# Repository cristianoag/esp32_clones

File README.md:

# The Retro Hacker Clone Series

The Retro Hacker Clone Series brings together hardware designs and source-available firmware to recreate and emulate classic computers from the 1980s and 1990s using modern ESP32-S3 based hardware.

 The board is designed to feel like a small retro computer rather than a bare dev board, and the firmwares are built to be practical, tweakable, and easy to build from a standard Git checkout.

At the moment the series includes eight emulator builds on the same ESP32-S3 board:

| Firmware | Covered machines | Project |
| --- | --- | --- |
| CP400 | Prologica CP400 / CoCo 2 | [Setup guide](software/esp32_cp400_emulator/README.md) and [change log](software/esp32_cp400_emulator/docs/log.md) |
| MSX | MSX1, MSX2, and MSX2+ | [Setup guide](software/esp32_msx_emulator/README.md) and [change log](software/esp32_msx_emulator/docs/log.md) |
| MSX TurboR (experimental) | Panasonic FS-A1ST | [Setup guide](software/esp32_msxturbor_emulator/README.md), [license report](software/esp32_msxturbor_emulator/docs/licenses.md) and [change log](software/esp32_msxturbor_emulator/docs/log.md) |
| TK90X / TK95 | Microdigital TK90X (48 KiB) and TK95 | [Setup guide](software/esp32_tk95_emulator/README.md) and [change log](software/esp32_tk95_emulator/docs/log.md) |
| Apple II | Generic Apple II+ and original Apple IIe | [Setup guide](software/esp32_apple2_emulator/README.md) and [change log](software/esp32_apple2_emulator/docs/log.md) |
| Macintosh Plus | Apple Macintosh Plus | [Setup guide](software/esp32_macplus_emulator/README.md) and [change log](software/esp32_macplus_emulator/docs/log.md) |
| Sega Master System | Sega Master System (NTSC / PAL) | [Setup guide](software/esp32_sms_emulator/README.md) and [change log](software/esp32_sms_emulator/docs/log.md) |
| Commodore 64 | Commodore 64 (PAL) | [Setup guide](software/esp32_c64_emulator/README.md), [licenses](software/esp32_c64_emulator/docs/licenses.md) and [change log](software/esp32_c64_emulator/docs/log.md) |

> **Development status:** all firmwares are under active development and at different maturity stages. The CP400 and MSX firmwares are the most mature; the others (including the experimental MSX TurboR) are earlier-stage and may be incomplete or change significantly.

All eight builds share the same board, VGA output, USB keyboard input, SD-card storage, and a simple F12 menu for setup and firmware updates.

## User guides

- [Quick Start](docs/quick-start.md): connect the monitor, keyboard and
  joysticks, turn on/reset the computer, and switch firmware through F12.
- [User Manual](docs/user-manual.md): SD-card preparation, controller
  compatibility, game-loading steps for all eight firmwares, and troubleshooting.

### Switching emulators

With the current updater and shared dual 4 MiB OTA layout installed, open
**F12 > Firmware update** in any emulator and select another emulator's
`.FLH` package. For example, MSX can install CP400, and CP400 can then
install Apple II. No renaming is needed. Copy the packages to the FAT32
card root (required by CP400's file picker), prepare the destination
emulator's ROMs using its setup guide, confirm the update and keep power
connected until the board restarts. The original FLH stays on the card.

Build packages with `make firmware` in each firmware folder. Older MSX,
TK and Apple updaters reject other emulator filenames: first update to
the current build of the **same** emulator. Older CP400 installations use
a smaller partition layout and require a **one-time UART upload** of a
current build before switching via SD. FLH updates replace only the
application, not the bootloader or partition table. Use current builds
for every destination so switching remains available after reboot.
Checksums detect corruption, not authenticity; install only trusted
firmware built for this board.

After building all eight packages, run
`powershell -ExecutionPolicy Bypass -File .\software\Test-FirmwareCompatibility.ps1`
to check the shared layout and all 64 source/destination combinations
against mock OTA storage. Physical-board switching still needs validation.

## Commodore 64

The [C64 firmware](software/esp32_c64_emulator/README.md) adapts the
CPU, CIA, VIC-II and SID from
[retroelec/T-HMI-C64](https://github.com/retroelec/T-HMI-C64) to the shared
VGA board. It includes a USB C64 keyboard matrix, two calibrated USB
joysticks with port swapping, PWM sound, PRG loading, read-only D64 program
extraction, the F12 configuration menu and interchangeable FLH firmware.
Supply your own BASIC, KERNAL and character ROMs. The initial version
does not emulate a 1541 drive, cartridges or tapes, and does not claim
cycle accuracy or verified physical-board performance.

## Why this exists

The goal is not to produce a display piece. This is meant to be a useful, buildable retro-computing emulation based platform: something that captures the character of a classic computer without needing a pile of original hardware on the bench.

The project sits between hardware design, emulator work, and preservation. It keeps the board layout, software, and documentation together in one place so someone can build, test, and modify it without digging through a dozen disconnected repos.

## CP400

The Prologica CP400 was one of the more recognizable Brazilian home computers of the 1980s. It was compatible with the Tandy/Radio Shack TRS-80 Color Computer 2, but it had its own industrial design, Brazilian-language software ecosystem, and local hardware expectations.

The [CP400 firmware](software/esp32_cp400_emulator/README.md) recreates that environment on ESP32-S3 hardware, including MC6809 emulation, VGA output, native USB keyboard support, joystick inputs, SD storage, virtual floppy handling, and the F12 configuration/update menu.

## MSX

The MSX has a very special place in Brazilian computing history. It officially arrived in Brazil in 1985 through two locally produced machines: the HotBit, from Sharp/Epcom, and the Expert, from Gradiente. At a time when Brazil’s computer market was heavily restricted and imported machines were difficult and expensive to obtain, the MSX became one of the country’s most important home-computing platforms. Its standardized architecture, large software library, expandability, and built-in BASIC introduced an entire generation not only to games, but also to programming, electronics, and computer technology. 

The [MSX firmware](software/esp32_msx_emulator/README.md) runs the original fMSX core on the same shared board. It includes multiple BIOS profiles for Omega MSX2+, Gradiente Expert 1.1, Sharp Hotbit 1.2, and Panasonic FS-A1WSX / FS-A1F / FS-A1FX.

The software supports the core MSX experience with USB keyboard input, graphics, sound, cartridge booting, and firmware updates through the on-screen menu. and... USB joystick support, of course.

The F12 Media menu attaches writable `.dsk` images to drives A/B and read-only `.cas` tapes, with ejection, tape rewind and optional saved boot defaults. Disk access requires a compatible user-supplied disk BIOS; see the [disk and tape setup guide](software/esp32_msx_emulator/README.md#disk-and-tape-images).

## MSX TurboR / Panasonic FS-A1ST

The experimental [MSX TurboR firmware](software/esp32_msxturbor_emulator/README.md)
recreates the Panasonic FS-A1ST using a source subset of blueMSX, separate
from the ordinary fMSX-based MSX build. It includes Z80/R800 switching,
DRAM mode, V9958 graphics, PSG, MSX-MUSIC, PCM output and writable
360/720 KiB `.dsk` images through the original disk interface.

Supply your own FS-A1ST firmware and Kanji ROMs under
`msxturbor/bios/fs-a1st` on the FAT32 card. See the
[SD card and ROM setup](software/esp32_msxturbor_emulator/README.md#prepare-the-sd-card),
[scope and limitations](software/esp32_msxturbor_emulator/README.md#implementation-scope-and-limitations)
and [licenses and provenance](software/esp32_msxturbor_emulator/docs/licenses.md).
The original BIOS boots into MSX BASIC in host tests; physical-board
performance, VGA/audio quality and firmware switching still require
validation. A1GT/MIDI and full-speed emulation are not claimed.

## TK90X / TK95

The Microdigital TK90X and TK95 brought the ZX Spectrum family of computers to Brazilian homes. The [TK firmware](software/esp32_tk95_emulator/README.md) emulates the TK95 and 48 KiB TK90X on the same shared ESP32-S3 board, using
the cycle-stepped chips Z80 core.

The firmware includes VGA output, USB keyboard input, beeper audio and two USB joystick ports with calibration and selectable Kempston, Sinclair 1/2 or Cursor interfaces. The F12 menu brings together machine and ROM selection, 50/60 Hz Microdigital ULA timing, Portuguese/Spanish ROM language selection, sound and volume, saved boot defaults, reset options and firmware updates.

Media support includes read-only standard `.tap` playback and loading 48K `.sna` and `.z80` snapshots. Supply legally obtained, raw 16 KiB ROMs at `tk\bios\tk95.rom` and `tk\bios\tk90.rom` on the FAT32 card; the `tk` folder can sit alongside `msx` and `cp400`. No ROM bytes are embedded in the firmware.

See the [SD card and ROM setup](software/esp32_tk95_emulator/README.md#sd-card-and-roms) and [keyboard guide](software/esp32_tk95_emulator/README.md#keyboard-and-joysticks) for the original TK keyword-entry conventions.

The initial release does not include AY audio, Betadisk, TZX, tape recording or snapshot saving, and does not claim full cycle accuracy. 

## Apple II

The [Apple II firmware](software/esp32_apple2_emulator/README.md) adds generic
Apple II+ (64 KiB with language card) and original Apple IIe (128 KiB)
profiles. It follows the shared standalone PlatformIO, board-driver, F12
configuration and FLH firmware-update conventions.

The initial integration uses
[codesafe/ESP32-VGA_AppleII_Emulator](https://github.com/codesafe/ESP32-VGA_AppleII_Emulator)
as its starting reference, with a cycle-stepped NMOS 6502 and additional
IIe banking and display support. VGA preserves the full width of
80-column text; USB keyboard, calibrated joystick/paddle input, speaker
audio and two read-only NIB Disk II drives are included.

Supply machine and Disk II ROMs under `apple2/bios` on SD. No ROMs or games
are distributed. Enhanced IIe/65C02 and Brazilian TK2000, TK3000/Compact,
MC-4000/Exato and Exato IIe profiles are not claimed as supported without
their required hardware and verified ROMs. See the
[scope and limitations](software/esp32_apple2_emulator/README.md#supported-media-and-limitations).
Physical-board validation is still pending.

## Macintosh Plus

The [Macintosh Plus firmware](software/esp32_macplus_emulator/README.md)
integrates a Musashi 68000 and Macintosh peripheral core with 4 MiB of
emulated RAM, a native 512x342 monochrome image centered on 640x480 VGA,
USB keyboard input, mono audio and the shared F12 menu and FLH updater.
A direct low-speed HID boot mouse connects to **joystick port 2**;
full-speed-only mice and USB hubs are unsupported.

Supply an unmodified 128 KiB Macintosh Plus ROM and a bootable whole
SCSI disk image under `macplus/bios` and `macplus/disks` on the FAT32 card.
No Apple ROM, operating system or disk image is bundled. See the
[SD card, ROM and disk setup](software/esp32_macplus_emulator/README.md#sd-card-and-rom),
[mouse compatibility](software/esp32_macplus_emulator/README.md#mouse-compatibility)
and [scope and validation](software/esp32_macplus_emulator/README.md#scope-and-validation).
This is an initial integration, not a claim of full-speed or cycle-accurate
emulation; floppy-media support is not implemented.

## Repository layout

```text
hardware/esp32_clones/          KiCad PCB and shared board files
hardware/esp32_clones/libraries Local KiCad symbols and footprints
hardware/esp32_clones/bom       Interactive BOM and BOM assets
hardware/cases/standard/       Parametric printed base, acrylic lid and manufacturing exports
software/esp32_cp400_emulator/  PlatformIO firmware for the CP400 build
software/esp32_msx_emulator/    MSX firmware and setup files
software/esp32_msxturbor_emulator/ MSX TurboR / Panasonic FS-A1ST firmware and setup files
software/esp32_tk95_emulator/   TK90X/TK95 firmware and setup files
software/esp32_apple2_emulator/ Apple II+/original IIe firmware and setup files
software/esp32_macplus_emulator/ Macintosh Plus firmware and setup files
images/                         Generated images and project documentation assets
```

## Board renderings

For the first enclosure prototype, see the
[standard case manufacturing files and engineering report](hardware/cases/standard/README.md).
P4 combines a printed base with easy-loading PCB nut traps, a screw-fastened
upper and a drilled 3 mm acrylic lid. Four M3 x 25 nylon screws pass down through
the acrylic into base nuts. Its vented alternative uses a separate matching
base with recessed bottom-entry screws and upper nuts. The acrylic cutting
pattern is [lid.dxf](hardware/cases/standard/lid.dxf); do not reuse the old
plain panel. See the report for dimensions and remaining physical-fit checks.

The Hotbit-inspired **Compact Classic C6** fits the same PCB in a
**124 x 74 x 39.1 mm** case, reducing the earlier Classic footprint by 26.9%.
It retains the miniature keyboard, photo-inspired colours and closed decorative
grille, with underside M3 cover screws. Use the matching
[base STL](hardware/cases/hb-8000/classic_base.stl) and
[upper STL](hardware/cases/hb-8000/classic_upper.stl); do not mix these with older
Classic or Wasteland halves. See the
[assembled/exploded preview](hardware/cases/hb-8000/classic_preview.png).
Print both STLs at 100%; the upper needs removable interior supports.
PCB screws remain M3 x 8 with 1 mm nylon washers; cover screws are M3 x 25 nylon,
with four M3 hex nuts for each set. Physical plug-fit and thermal tests are
still required; the decorative grille is not a ventilation opening.

The [Sony S2](hardware/cases/sony/README.md),
[Panasonic P2](hardware/cases/panasonic/README.md) and
[Apple II A3](hardware/cases/apple2/README.md) now share the C6 base and its
bottom-entry shell fastening. Their matching uppers replace the old clip joints.

The [Mac Plus-inspired M1](hardware/cases/mac/README.md) uses the same C6 base
under a **124 x 74 x 146.1 mm upright tower**, with a separate dark decorative
screen and miniature keyboard. Its blind floppy-slot detail, top grilles and
handle-shaped recess follow the supplied visual reference; no working display,
keyboard electronics or load-bearing handle is included. See the
[assembly and print-layout preview](hardware/cases/mac/mac_preview.png).

The [CP400-inspired CP1](hardware/cases/cp400/README.md) also reuses the C6
base in the compact **124 x 74 x 39.1 mm** envelope. Its left keyboard, raised
right panel and horizontal rear grilles follow the supplied photograph.
Integral and separate-keyboard upper options are available; red/green/cyan
accents in the [preview](hardware/cases/cp400/cp400_preview.png) are a painting
guide, not separate key pieces.

The [Master System-inspired SMS1](hardware/cases/sms/README.md) uses the same
C6 base and **124 x 74 x 39.1 mm** envelope, with an angular black console
shell and one separately printed red top-panel/front-stripe insert.
Cartridge/card slots and control shapes are decorative; no joystick or
controller is modelled. See the
[assembly and print-layout preview](hardware/cases/sms/sms_preview.png).

The PCB below is the current KiCad board layout for the shared ESP32 clone board. The front and back views are generated directly from the project PCB.

<div align="center">

</div>

For the full component-by-component assembly view, open the [interactive BOM](https://htmlpreview.github.io/?https://raw.githubusercontent.com/cristianoag/esp32_clones/blob/main/hardware/esp32_clones/bom/ibom.html).

## Hardware summary

The board is built around an ESP32-S3 DevKitC-style N16R8 module with 16 MB flash and 8 MB OPI PSRAM. It includes VGA output, a USB keyboard port, SD/MMC storage, a mono audio output, and a compact layout intended to behave more like a small computer than a bare dev board.

The shared board is used by all six firmware projects, and the pin mapping is documented in the [MSX hardware section](software/esp32_msx_emulator/README.md#hardware), the [MSX TurboR hardware section](software/esp32_msxturbor_emulator/README.md#hardware-and-dependencies), the [TK hardware section](software/esp32_tk95_emulator/README.md#hardware), the [Apple II hardware section](software/esp32_apple2_emulator/README.md#hardware) and the [Macintosh Plus hardware section](software/esp32_macplus_emulator/README.md#hardware).

## BOM and purchasing

This is the current BOM for the board as defined in the KiCad project. The table is meant to be a quick parts reference for ordering and build prep.

| Component | Description | Qty | Package | AliExpress |
| --- | --- | ---: | --- | --- |
| C1 | 220 µF electrolytic capacitor | 1 | 6.3x3 mm | [AliExpress](https://s.click.aliexpress.com/e/_c3vZZzuN) |
| C2 | 10 µF electrolytic capacitor | 1 | 5x4.5 mm | [AliExpress](https://s.click.aliexpress.com/e/_c3vZZzuN) |
| C4 | 100 nF ceramic capacitor | 1 | 0805 | [AliExpress](https://s.click.aliexpress.com/e/_c31gzw17) |
| C6 | 47 nF ceramic capacitor | 1 | 0805 | [AliExpress](https://s.click.aliexpress.com/e/_c31gzw17) |
| F1 | Resettable fuse / polyfuse | 1 | 1210 | [AliExpress](https://s.click.aliexpress.com/e/_c36cHi81) |
| J1 | DC barrel jack | 1 | Horizontal | [AliExpress](https://s.click.aliexpress.com/e/_c3D102dx) |
| J2 | Micro SD card socket | 1 | uSD | [AliExpress](https://s.click.aliexpress.com/e/_c3odXI41) |
| J3 | 3.5 mm audio jack | 1 | PJ-307 | [AliExpress](https://s.click.aliexpress.com/e/_c4DX94lF) |
| J4 | 12V power header / connector | 1 | PS-12E05 | [AliExpress](https://s.click.aliexpress.com/e/_c42cnGRn) |
| J5 | 5V power header / connector | 1 | PS-22F05 | [AliExpress](https://s.click.aliexpress.com/e/_c35YnsCh) |
| J6–J8 | USB-A connector | 3 | TE 6364372-2 | [AliExpress](https://s.click.aliexpress.com/e/_c4afTAHb) |
| J9 | DB15 video connector | 1 | D-sub 15-pin | [AliExpress](https://s.click.aliexpress.com/e/_c3K7eRWv) |
| R1, R4, R7 | 10 kΩ resistor | 3 | 0805 | [AliExpress](https://s.click.aliexpress.com/e/_c2zrvGiH) |
| R8, R10, R12 | 1.2 kΩ resistor | 3 | 0805 | [AliExpress](https://s.click.aliexpress.com/e/_c2zrvGiH) |
| R9, R11, R13 | 560 Ω resistor | 3 | 0805 | [AliExpress](https://s.click.aliexpress.com/e/_c2zrvGiH) |
| R2, R5 | 330 Ω resistor | 2 | 0805 | [AliExpress](https://s.click.aliexpress.com/e/_c2zrvGiH) |
| U1 | ESP32-S3-WROOM-1 module | 1 | ESP32-S3-WROOM-1 | [AliExpress](https://s.click.aliexpress.com/e/_c2uppnEv) |

## Firmware build notes

All six firmware projects use PlatformIO with the Arduino framework and a pinned `espressif32@6.11.0` platform. From the project directory you want to use, run:

```powershell
Set-Location .\software\esp32_cp400_emulator
# or:
# Set-Location .\software\esp32_msx_emulator
# or:
# Set-Location .\software\esp32_msxturbor_emulator
# or:
# Set-Location .\software\esp32_tk95_emulator
# or:
# Set-Location .\software\esp32_apple2_emulator
# or:
# Set-Location .\software\esp32_macplus_emulator

make firmware
```

The build produces FLH packages for each target; the project directories keep their own firmware images and configuration.
From `software`, run `make` to prepare the shared SD-card tree and copy each
emulator's highest-versioned `dist\ESP32_*-X.YY.FLH` package only to the root of
`software\sdcard`. Firmware packages are copied
after merging the SD-card trees, including with parallel `make`.
Run `make firmware` there to copy packages only, or `make sdcard`
to prepare the SD-card tree only. Packages are not rebuilt; if any emulator is
missing a package, copying fails before any firmware files are deleted or copied.
Before copying, all FLH files directly in the shared SD-card root are deleted,
leaving only the latest package for each emulator. Emulator project roots and
`dist` archives are left unchanged, as are non-FLH files and nested folders
during firmware copying.
Each firmware directory includes its own board definitions and required
library sources and can be copied and compiled independently of the others.
All six still require PlatformIO and the configured ESP32 toolchain.

## ROMs and original software

Original CP400, CoCo, MSX, MSX TurboR, TK90X/TK95, ZX Spectrum, Apple II, Macintosh Plus, BASIC, cartridge, cassette, floppy and hard-disk software may still be copyrighted. This repository is for original hardware, firmware, and project files. Use legally obtained ROMs and software images when needed.

The CP400 firmware loads its BIOS files from `software/esp32_cp400_emulator/sdcard/cp400/bios`. Copy the `cp400` folder to the root of the microSD card so the firmware can read the BASIC, Extended BASIC, and CP400 or CoCo disk controller ROM selected in the F12 menu.

## Historical notes

The CP400 was part of the wider Brazilian TRS-Color ecosystem, the MSX line became one of the most important home computer families in Brazil, and Microdigital's TK90X and TK95 connected Brazilian users to the ZX Spectrum ecosystem. This project sits at the intersection of those histories: a practical board, six emulator builds, and a small bit of preservation work for machines that still matter to a lot of people.

## References

- [Prologica CP-400](https://en.wikipedia.org/wiki/Prol%C3%B3gica_CP-400)
- [CP400](https://pt.wikipedia.org/wiki/CP400)
- [TRS-80 Color Computer](https://en.wikipedia.org/wiki/TRS-80_Color_Computer)
- [MSX](https://en.wikipedia.org/wiki/MSX)
- [fMSX by Marat Fayzullin](https://fms.komkon.org/fMSX/)
- [TK90X](https://en.wikipedia.org/wiki/TK90X)
- [TK95](https://en.wikipedia.org/wiki/TK95)
- [ESPectrum reference emulator](https://github.com/EremusOne/ESPectrum)
- [chips Z80 core](https://github.com/floooh/chips)
- [Prologica](https://pt.wikipedia.org/wiki/Prol%C3%B3gica)
- [Datassette](https://datassette.org/)

## License

All hardware and firmware binaries in this repository are released under the Creative Commons Attribution-NonCommercial-ShareAlike 4.0 International license. Personal builds and community tinkering are encouraged, but commercial use or resale requires explicit authorization from the author.

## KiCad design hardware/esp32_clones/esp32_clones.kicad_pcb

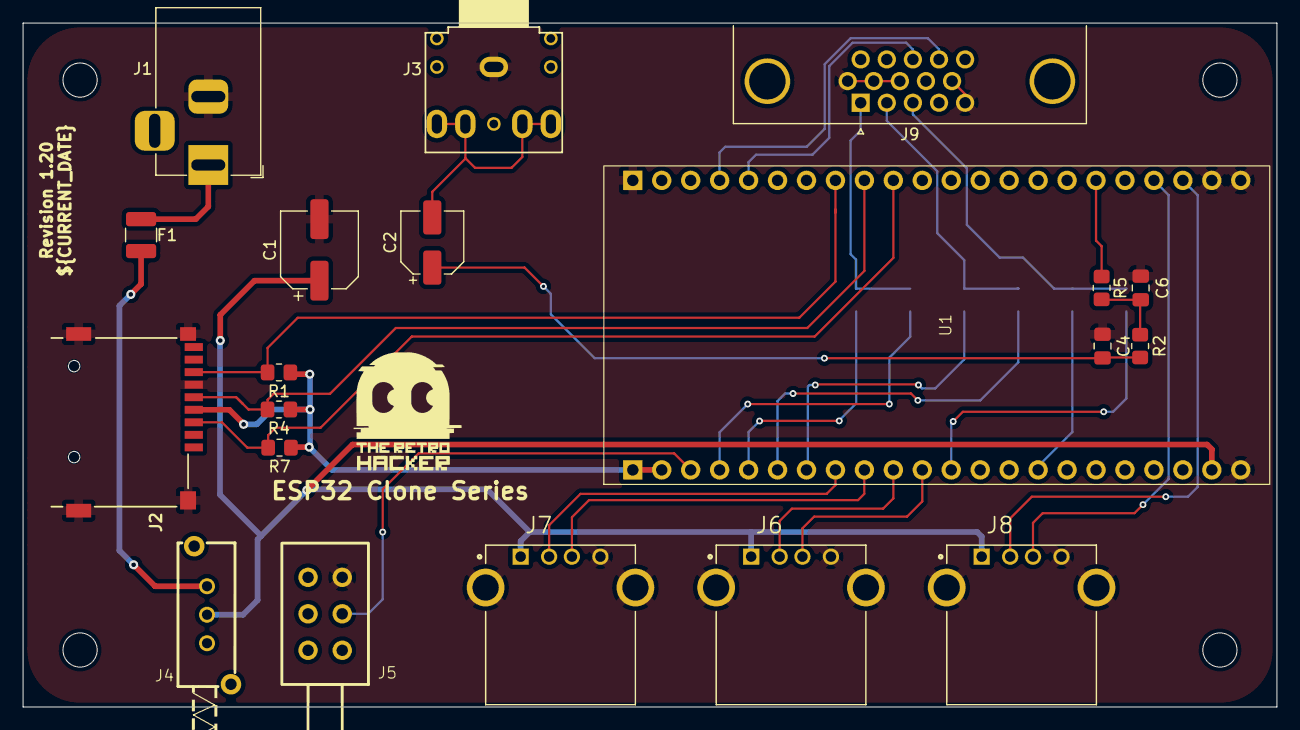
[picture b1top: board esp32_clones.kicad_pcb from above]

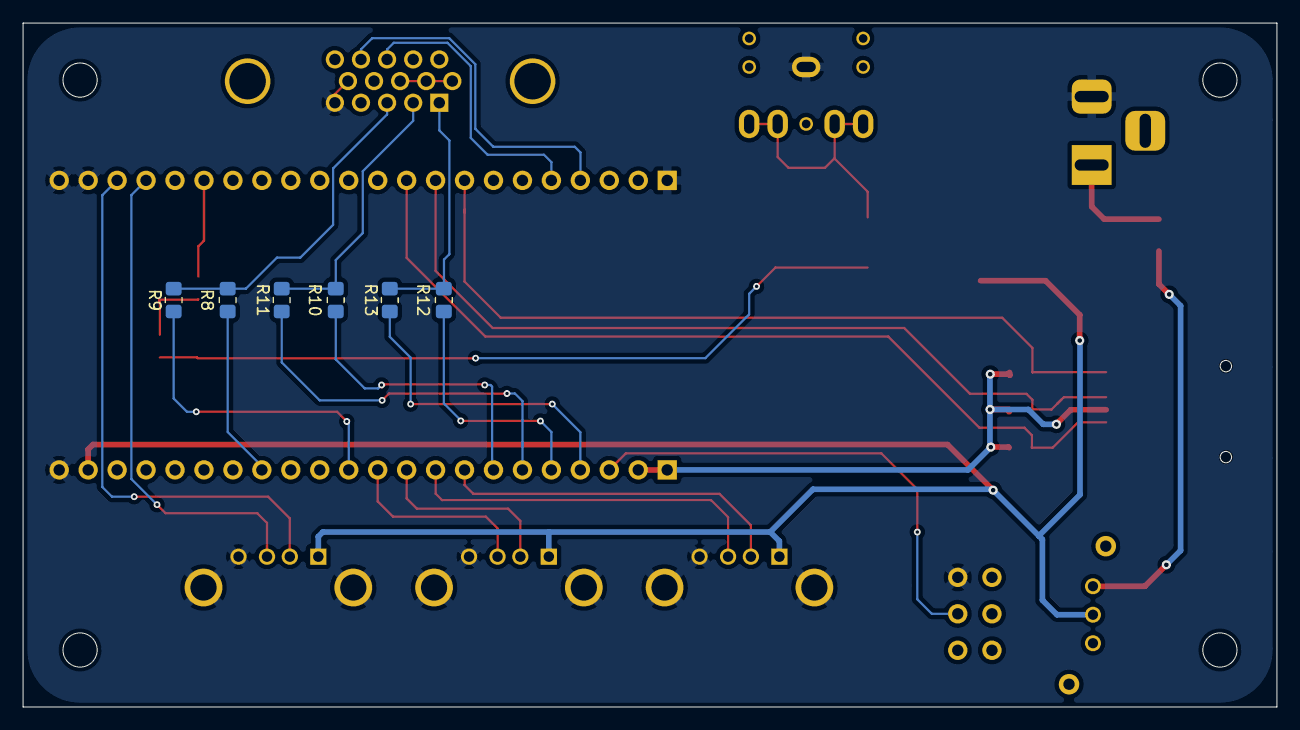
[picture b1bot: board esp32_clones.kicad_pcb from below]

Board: 2 copper layers, 110.0 x 60.0 mm, 26 parts (6 on the bottom side), 30 nets.

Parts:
C1: 220UF; CP_Elec_6.3x3
C2: 10UF; CP_Elec_5x4.5
C4: 100NF; C_0805_2012Metric_Pad1.18x1.45mm_HandSolder
C6: 47NF; C_0805_2012Metric_Pad1.18x1.45mm_HandSolder
F1: Fuse; Fuse_1210_3225Metric
J1: Barrel_Jack; BarrelJack_Horizontal
J2: Micro_SD_Card; Conn_uSDcard
J3: AudioJack2_Ground; PJ-307
J4: PS-12E05
J5: PS-22F05
J6, J7, J8: USB_A; TE_6364372-2
J9: DA15_Pins; DSUB-15-HD_Socket_Horizontal_P2.29x1.90mm_EdgePinOffset3.03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
R1, R4, R7: 10K; R_0805_2012Metric_Pad1.20x1.40mm_HandSolder
R2, R5: 330; R_0805_2012Metric_Pad1.20x1.40mm_HandSolder
R8, R10, R12: 1.2K; R_0805_2012Metric_Pad1.20x1.40mm_HandSolder
R9, R11, R13: 560; R_0805_2012Metric_Pad1.20x1.40mm_HandSolder
U1: ESP32-S3-WROOM-1

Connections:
+3.3V: J2.4 (VDD), R1.1, R4.1, R7.1, U1.23 (3V3), U1.24 (3V3)
+5V: C1.1, J4.2, J6.1 (VBUS), J7.1 (VBUS), J8.1 (VBUS), U1.43 (5V)
GND: C1.2, C4.2, C6.2, J1.2, J2.6 (VSS), J3.G, J5.3, J6.4 (GND), J6.5 (Shield), J7.4 (GND), J7.5 (Shield), J8.4 (GND), J8.5 (Shield), J9.5, J9.6, J9.7, J9.8, J9.10, U1.1 (GND), U1.2 (GND), U1.22 (GND), U1.44 (GND)
unnamed: C2.1, C4.1, R2.2
unnamed: C2.2, J3.S, J3.T
unnamed: C6.1, R2.1, R5.2
unnamed: F1.1, J1.1
unnamed: F1.2, J4.1
unnamed: J2.5 (CLK), R4.2, U1.14 (IO39)
unnamed: J2.3 (CMD), R7.2, U1.13 (IO38)
unnamed: J2.7 (DAT0), R1.2, U1.15 (IO40)
unnamed: J6.3 (D+), U1.33 (IO18)
unnamed: J6.2 (D-), U1.32 (IO17)
unnamed: J7.3 (D+), U1.31 (IO16)
unnamed: J7.2 (D-), U1.30 (IO15)
unnamed: J8.3 (D+), U1.4 (I020)
unnamed: J8.2 (D-), U1.3 (IO19)
unnamed: J9.13, U1.18 (IO02)
unnamed: J9.14, U1.19 (IO01)
unnamed: J9.1, R12.1, R13.2
unnamed: J9.2, R10.1, R11.2
unnamed: J9.3, R8.1, R9.2
unnamed: R13.1, U1.26 (IO04)
unnamed: R12.2, U1.27 (IO05)
unnamed: R11.1, U1.28 (IO06)
unnamed: R10.2, U1.29 (IO07)
unnamed: R9.1, U1.34 (IO08)
unnamed: R8.2, U1.37 (IO09)
unnamed: R5.1, U1.6 (IO47)
unnamed: J5.2, U1.25 (RST)

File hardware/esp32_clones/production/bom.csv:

Designator,Footprint,Quantity,Value,LCSC Part #
C1,CP_Elec_6.3x3,1,220UF,
C2,CP_Elec_5x4.5,1,10UF,
C4,0805,1,100NF,
C6,0805,1,47NF,
F1,1210,1,Fuse,
J1,BarrelJack_Horizontal,1,Barrel_Jack,
J2,Conn_uSDcard,1,Micro_SD_Card,
J3,PJ-307,1,AudioJack2_Ground,
J4,PS-12E05,1,~,
J5,PS-22F05,1,~,
"J6, J7, J8",TE_6364372-2,3,USB_A,
J9,DSUB-15-HD_Socket_Horizontal_P2.29x1.90mm_EdgePinOffset3.03mm_Housed_MountingHolesOffset4.94mm,1,DA15_Pins,
"R1, R4, R7",0805,3,10K,
"R10, R12, R8",0805,3,1.2K,
"R11, R13, R9",0805,3,560,
"R2, R5",0805,2,330,
U1,ESP32-S3-WROOM-1,1,~,

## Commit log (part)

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2026-06-25 Add font data and testing documentation
    - Added CoCO2_3_Fonts.txt containing font data for the emulator.
    - Created README file in the test directory to explain the purpose of the directory and provide information on PlatformIO Unit Testing.
    - Introduced ScrapBook.txt with various BASIC programs and notes related to disk transactions and graphics modes.
2026-06-30 Refactor code structure for improved readability and maintainability

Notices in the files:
hardware/esp32_clones/esp32_clones.kicad_pcb:
This work is licensed under a
